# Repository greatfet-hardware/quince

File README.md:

# Quince
a 2.4 GHz SDR neighbor for GreatFET using 1-bit ADCs

Quince is a GreatFET neighbor that serves as a Software Defined Radio (SDR) receiver for the 2.4 GHz band using a 1-bit sampling technique.  It is intended specifically to enable all-channel Bluetooth monitoring, but it should support additional uses.

Quince features the TLV3502 dual comparator and an RF section based on the AD8347 quadrature demodulator.  Synthesis of a 2.4 GHz Local Oscillator (LO) is provided by ADF4360-0.  The 1-bit quadrature signals are sampled at 80+ Msps by the SGPIO peripheral on [Azalea](https://github.com/greatfet-hardware/azalea).

Channelization and demodulation are done in software on the host computer, but it may be necessary to add an FPGA to Quince in order to achieve real-time simultaneous monitoring of all Bluetooth channels.  The host software will likely be a rewrite of [gr-bluetooth](https://github.com/greatscottgadgets/gr-bluetooth) using [libbtbb](https://github.com/greatscottgadgets/libbtbb) (the core of software for [Ubertooth](https://greatscottgadgets.com/ubertoothone/)).

## Project Status

The first hardware prototype that achieves proof-of-concept has been assembled.  Software work is required before determining what changes are needed in the next hardware revision.

## Viewing or Modifying the Design

Required KiCad dependency:

https://github.com/greatscottgadgets/gsg-kicad-lib

If you are using git, the preferred way to install gsg-kicad-lib is to use the
submodule:

```
git submodule init && git submodule update
```

## Hardware Development Notes

Lower cost comparators that may have sufficient bandwidth:
* TLV3202, comparator, $0.60
* NCS2250, single, $0.20

It might be more cost-effective to use a wireless transmitter or transceiver IC to generate the LO, such as:
* CC2500
* ADF7242 (used on [Lucky Bamboo](https://github.com/greatfet-hardware/luckybamboo))

As an alternative to the comparators (and possibly to the quadrature demodulator as well) we may investigate the use of LVDS input on an FPGA.  This would be the preferred solution if an FPGA ends up on the board anyway for channelization.

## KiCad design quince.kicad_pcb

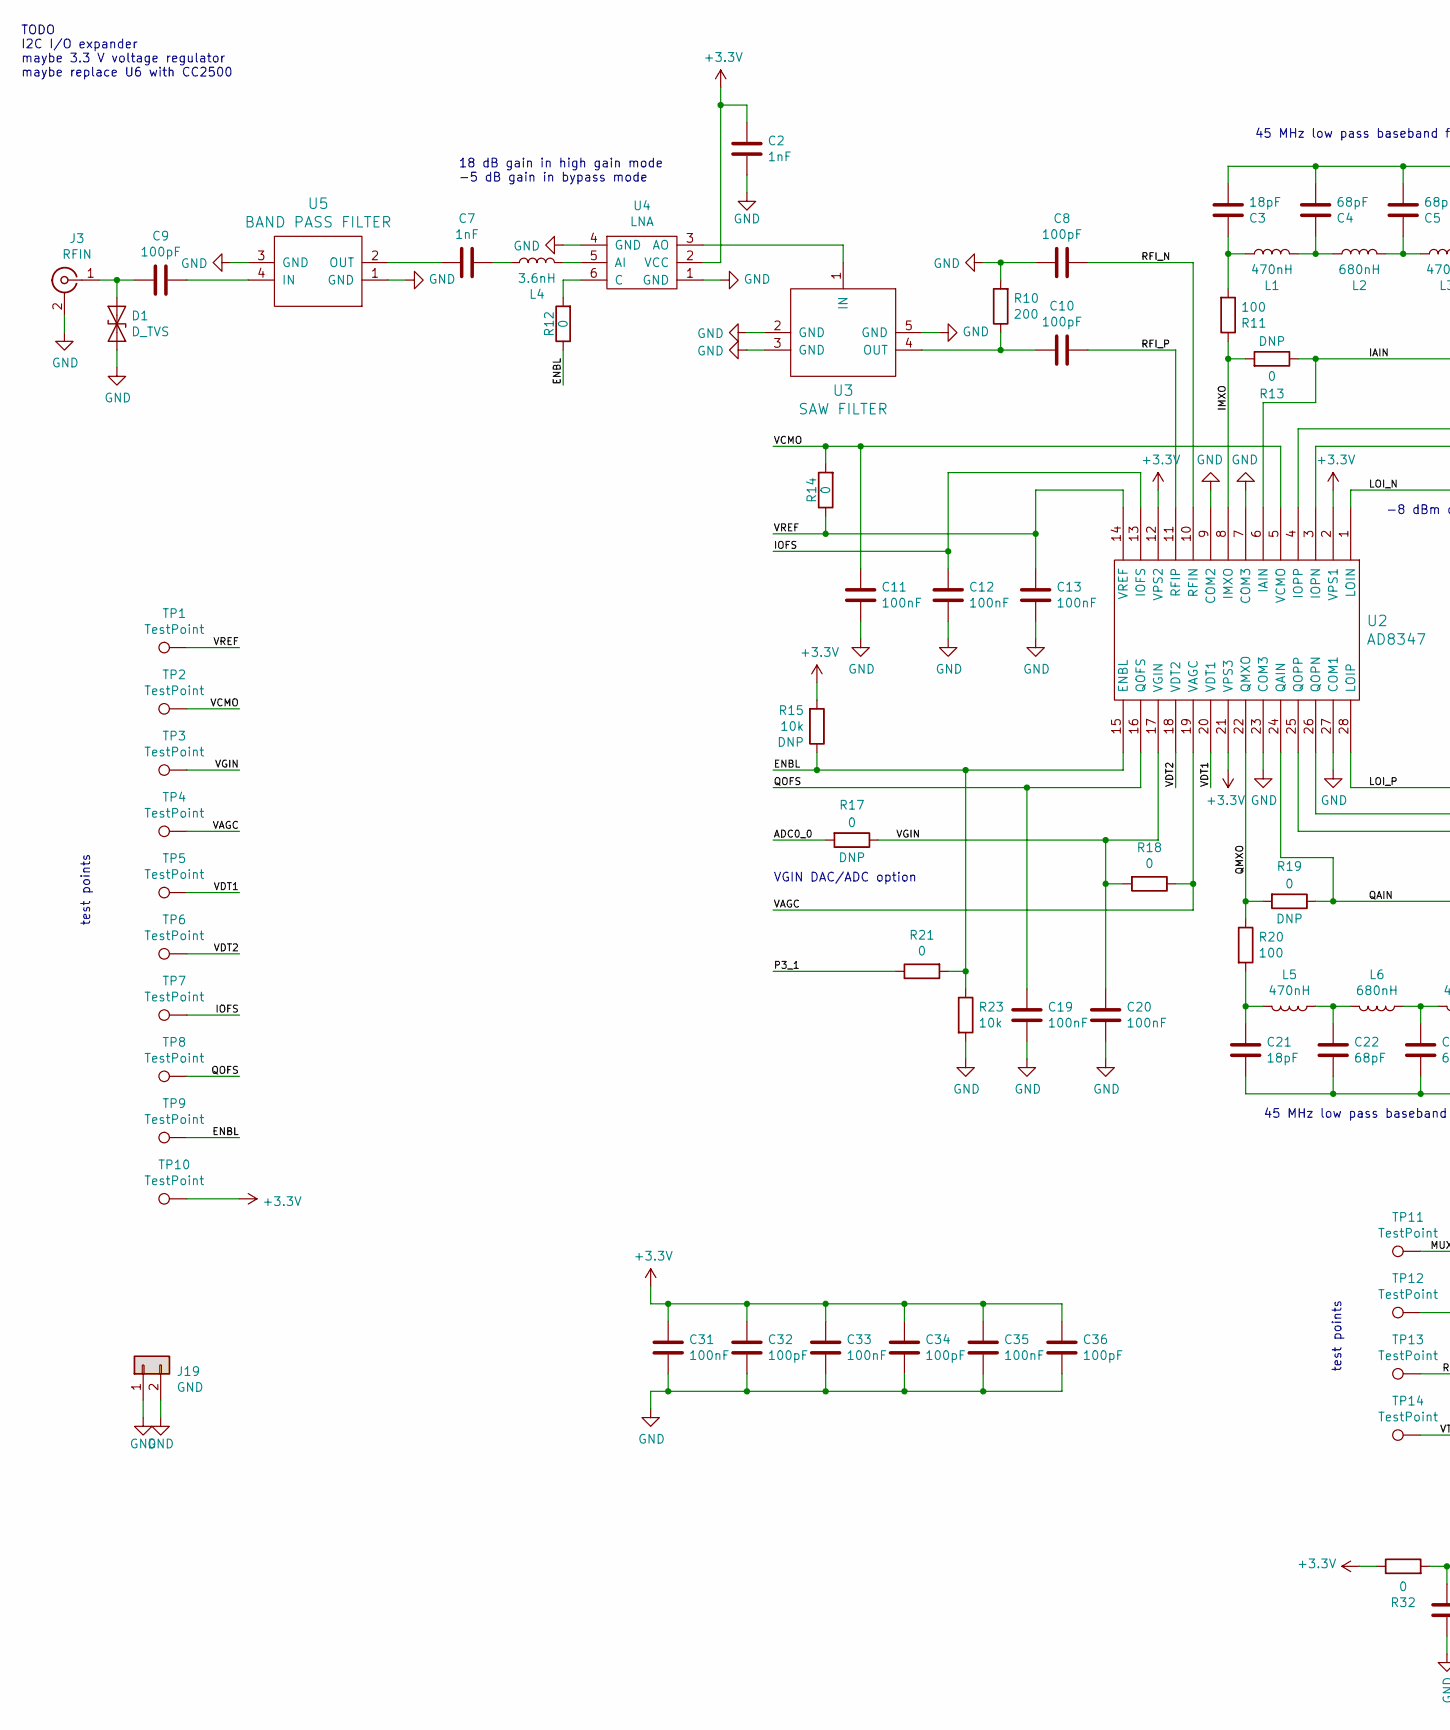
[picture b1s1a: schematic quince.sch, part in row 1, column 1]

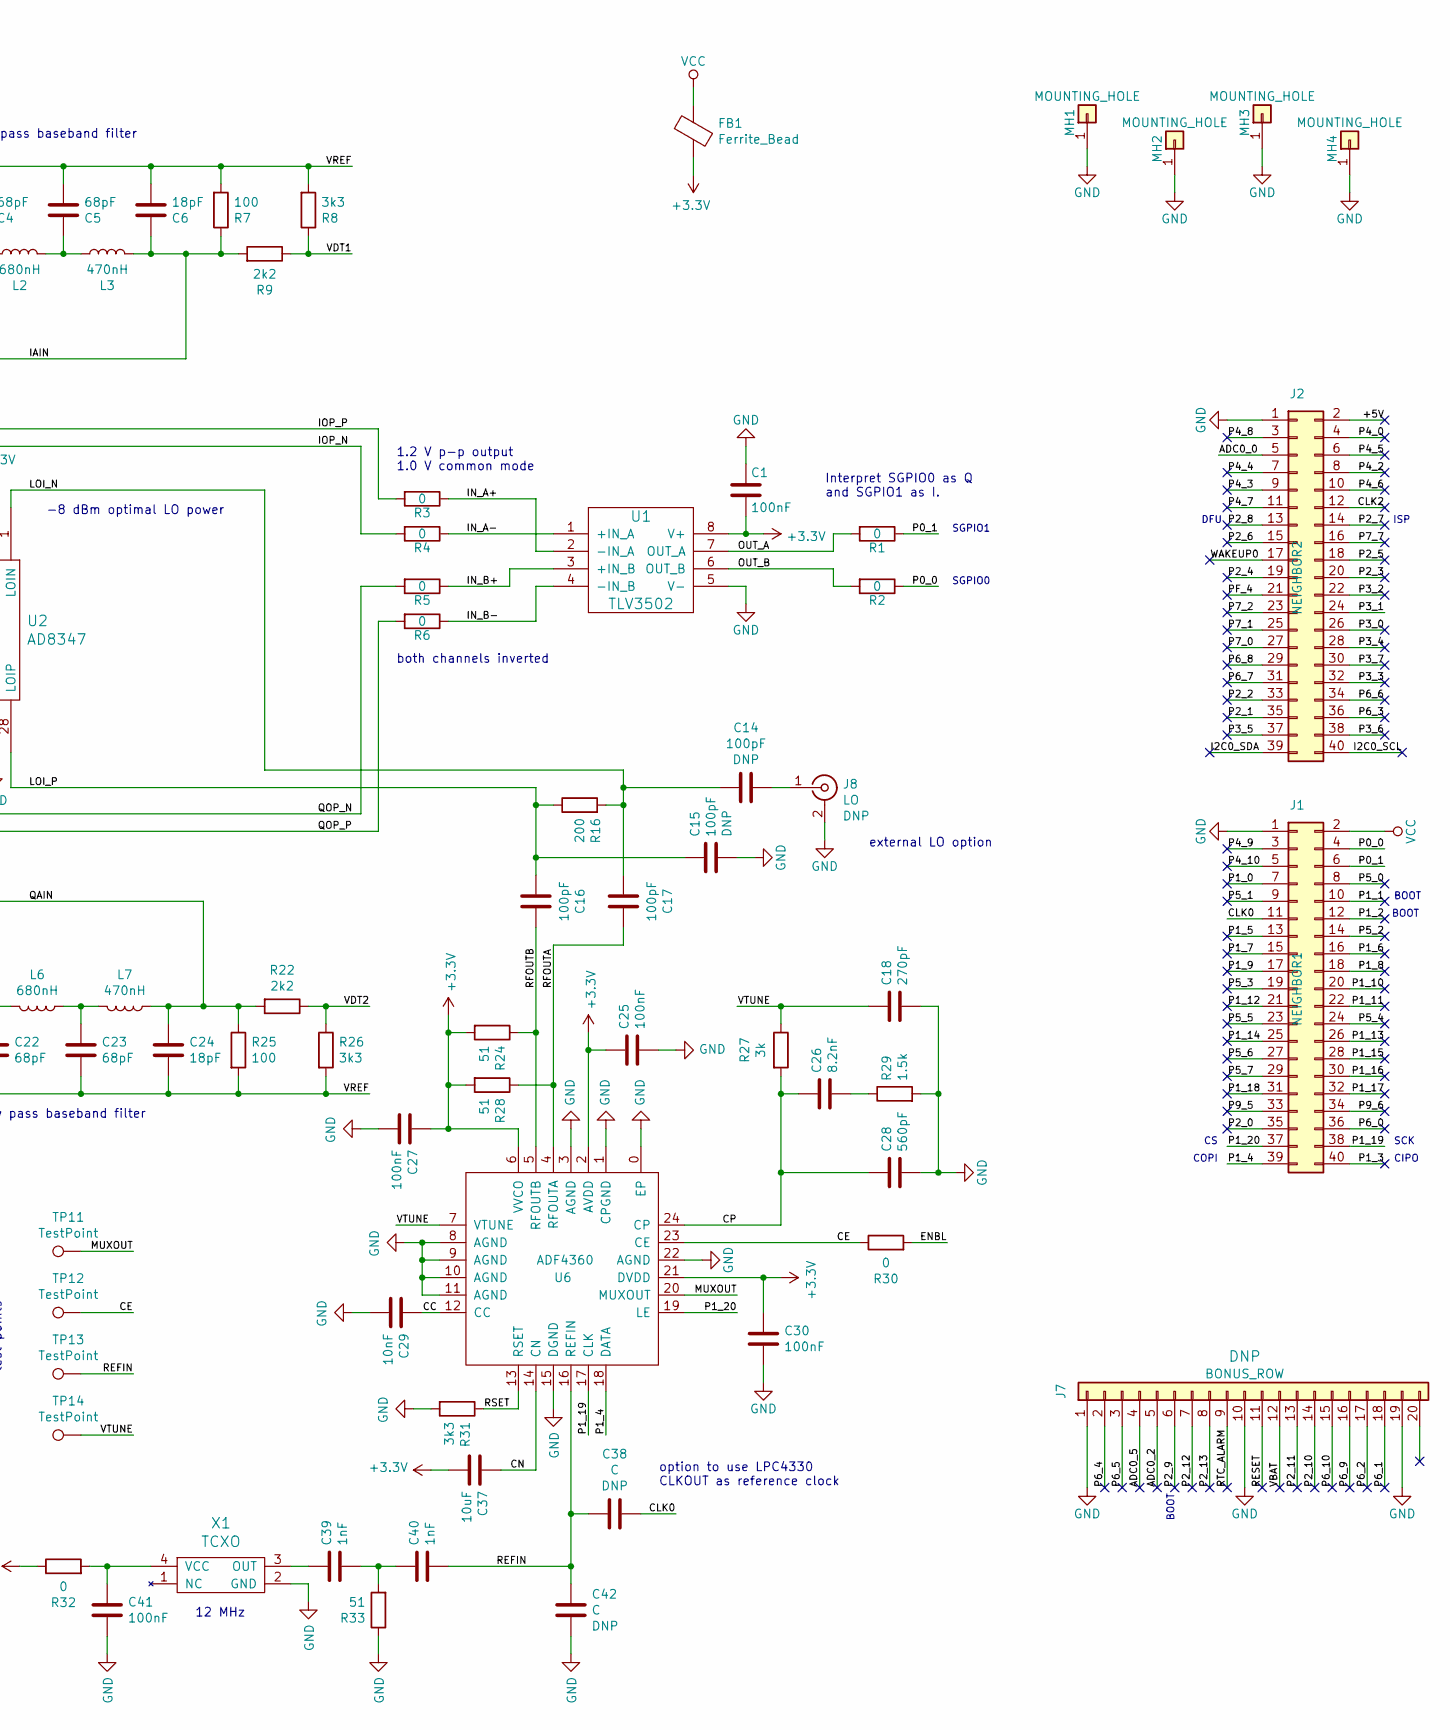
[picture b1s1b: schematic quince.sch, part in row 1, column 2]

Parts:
C1, C11, C12, C13, C19, C20, C25, C27, C30, C31, C33, C35, C41: 100nF; 0402; Part Number CL05A104MP5NNNC
C2, C7, C39, C40: 1nF; 0402; Part Number UMK105B7102KV-F
C3, C6, C21, C24: 18pF; 0402; Part Number CC0402JRNPO9BN180
C4, C5, C22, C23: 68pF; 0402; Part Number CL05C680JB5NNNC
C8, C9, C10, C14, C15, C16, C17, C32, C34, C36: 100pF; 0402; Part Number CL05C101JB5NNNC
C18: 270pF; 0402; Part Number CL05B271KB5NNNC
C26: 8.2nF; 0402; Part Number CC0402KRX7R7BB822
C28: 560pF; 0402; Part Number CL05B561KB5NNNC
C29: 10nF; 0402; Part Number CL05B103KB5NNNC
C37: 10uF; 0805; Part Number CL21A106KPFNNNG
C38, C42: C; 0402
D1: D_TVS; 0402; Part Number LXES15AAA1-153
FB1: Ferrite_Bead; 0805; Part Number BLM21PG221SN1D
J1: NEIGHBOR1; HEADER-2x20; Part Number SSQ-120-23-G-D
J2: NEIGHBOR2; HEADER-2x20; Part Number SSQ-120-23-G-D
J3: RFIN; SMA-EDGE; Part Number CONREVSMA003.062
J7: BONUS_ROW; HEADER-1x20; Part Number SSQ-120-23-G-S
J8: LO; SMA-VERTICAL; Part Number 5-1814832-1
J19: GND; HEADER-1x2
L1, L3, L5, L7: 470nH; 0402; Part Number LK1005R47K-TV
L2, L6: 680nH; 0402; Part Number LK1005R68K-TV
L4: 3.6nH; 0402; Part Number HK10053N6S-T
MH1, MH2, MH3, MH4: MOUNTING_HOLE; HOLE126MIL-COPPER
R1, R2, R3, R4, R5, R6, R12, R13, R14, R17, R18, R19, R21, R30, R32: 0; 0402; Part Number RC0402JR-070RL
R7, R11, R20, R25: 100; 0402; Part Number RC0402JR-07100RL
R8, R26, R31: 3k3; 0402; Part Number RC0402JR-073K3L
R9, R22: 2k2; 0402; Part Number RC0402JR-072K2L
R10, R16: 200; 0402; Part Number RC0402JR-07200RL
R15, R23: 10k; 0402; Part Number RC0402JR-0710KL
R24, R28, R33: 51; 0402; Part Number RC0402JR-0751RL
R27: 3k; 0402; Part Number RC0402JR-073KL
R29: 1.5k; 0402; Part Number RC0402JR-071K5L
TP1, TP2, TP3, TP4, TP5, TP6, TP7, TP8, TP9, TP10, TP11, TP12, TP13, TP14: TestPoint; TESTPOINT-50MIL
U1: TLV3502; SOIC8-154; Part Number TLV3502AIDR
U2: AD8347; TSSOP28; Part Number AD8347ARUZ-REEL7
U3: SAW FILTER; B9413; Part Number B39242B9413K610
U4: LNA; BGA7H1N6; Part Number BGA5H1BN6E6327XTSA1
U5: BAND PASS FILTER; 2450BP39D100C; Part Number 2450BP39D100CE
U6: ADF4360; QFN24-4; Part Number ADF4360-0BCPZ
X1: TCXO; XTAL5.0x3.2mm; Part Number FT5HNBPK12.0-T1

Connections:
+3V3: C1.2, C2.2, C25.1, C27.1, C30.1, C31.1, C32.2, C33.1, C34.2, C35.1, C36.2, C37.2, FB1.2, R15.2, R24.2, R28.2, R32.1, TP10.1, U1.8 (V+), U2.2 (VPS1), U2.12 (VPS2), U2.21 (VPS3), U4.2 (VCC), U6.2 (AVDD), U6.6 (VVCO), U6.21 (DVDD)
/+5V: J2.2
/ADC0_0: J2.5, R17.2
/ADC0_2: J7.5
/ADC0_5: J7.4
/CC: C29.1, U6.12 (CC)
/CE: R30.1, TP12.1, U6.23 (CE)
/CLK0: C38.2, J1.11
/CLK2: J2.12
/CN: C37.1, U6.14 (CN)
/CP: C26.2, C28.2, R27.2, U6.24 (CP)
/ENBL: R12.1, R15.1, R21.2, R23.1, R30.2, TP9.1, U2.15 (ENBL)
/I2C0_SCL: J2.40
/I2C0_SDA: J2.39
/IAIN: C6.1, L3.1, R7.1, R9.2, R13.1, U2.6 (IAIN)
/IMXO: R11.1, R13.2, U2.8 (IMXO)
/IN_A+: R3.1, U1.2 (-IN_A)
/IN_A-: R4.1, U1.1 (+IN_A)
/IN_B+: R5.1, U1.3 (+IN_B)
/IN_B-: R6.1, U1.4 (-IN_B)
/IOFS: C12.1, TP7.1, U2.13 (IOFS)
/IOP_N: R4.2, U2.3 (IOPN)
/IOP_P: R3.2, U2.4 (IOPP)
/LOI_N: C14.2, C17.2, R16.2, U2.1 (LOIN)
/LOI_P: C15.2, C16.2, R16.1, U2.28 (LOIP)
/MUXOUT: TP11.1, U6.20 (MUXOUT)
/OUT_A: R1.2, U1.7 (OUT_A)
/OUT_B: R2.2, U1.6 (OUT_B)
/P0_0: J1.4, R2.1
/P0_1: J1.6, R1.1
/P1_0: J1.7
/P1_1: J1.10
/P1_2: J1.12
/P1_3: J1.40
/P1_4: J1.39, U6.18 (DATA)
/P1_5: J1.13
/P1_6: J1.16
/P1_7: J1.15
/P1_8: J1.18
/P1_9: J1.17
/P1_10: J1.20
/P1_11: J1.22
/P1_12: J1.21
/P1_13: J1.26
/P1_14: J1.25
/P1_15: J1.28
/P1_16: J1.30
/P1_17: J1.32
/P1_18: J1.31
/P1_19: J1.38, U6.17 (CLK)
/P1_20: J1.37, U6.19 (LE)
/P2_0: J1.35
/P2_1: J2.35
/P2_2: J2.33
/P2_3: J2.20
/P2_4: J2.19
/P2_5: J2.18
/P2_6: J2.15
/P2_7: J2.14
/P2_8: J2.13
/P2_9: J7.6
/P2_10: J7.14
/P2_11: J7.13
/P2_12: J7.7
/P2_13: J7.8
/P3_0: J2.26
/P3_1: J2.24, R21.1
/P3_2: J2.22
/P3_3: J2.32
/P3_4: J2.28
/P3_5: J2.37
/P3_6: J2.38
/P3_7: J2.30
/P4_0: J2.4
/P4_2: J2.8
/P4_3: J2.9
/P4_4: J2.7
/P4_5: J2.6
/P4_6: J2.10
/P4_7: J2.11
/P4_8: J2.3
/P4_9: J1.3
/P4_10: J1.5
/P5_0: J1.8
/P5_1: J1.9
/P5_2: J1.14
/P5_3: J1.19
/P5_4: J1.24
/P5_5: J1.23
/P5_6: J1.27
/P5_7: J1.29
/P6_0: J1.36
/P6_1: J7.18
/P6_2: J7.17
/P6_3: J2.36
/P6_4: J7.2
/P6_5: J7.3
/P6_6: J2.34
/P6_7: J2.31
/P6_8: J2.29
/P6_9: J7.16
/P6_10: J7.15
/P7_0: J2.27
/P7_1: J2.25
/P7_2: J2.23
/P7_7: J2.16
/P9_5: J1.33
/P9_6: J1.34
/PF_4: J2.21
/QAIN: C24.1, L7.1, R19.1, R22.2, R25.1, U2.24 (QAIN)
/QMXO: R19.2, R20.1, U2.22 (QMXO)
/QOFS: C19.1, TP8.1, U2.16 (QOFS)
/QOP_N: R5.2, U2.26 (QOPN)
/QOP_P: R6.2, U2.25 (QOPP)
/REFIN: C38.1, C40.2, C42.2, TP13.1, U6.16 (REFIN)
/RESET: J7.11
/RFI_N: C8.1, U2.10 (RFIN)
/RFI_P: C10.1, U2.11 (RFIP)
/RFOUTA: C17.1, R28.1, U6.4 (RFOUTA)
/RFOUTB: C16.1, R24.1, U6.5 (RFOUTB)
/RSET: R31.1, U6.13 (RSET)
/RTC_ALARM: J7.9
/VAGC: R18.1, TP4.1, U2.19 (VAGC)
/VBAT: J7.12
/VCMO: C11.1, R14.2, TP2.1, U2.5 (VCMO)
/VDT1: R8.1, R9.1, TP5.1, U2.20 (VDT1)
/VDT2: R22.1, R26.1, TP6.1, U2.18 (VDT2)
/VGIN: C20.1, R17.1, R18.2, TP3.1, U2.17 (VGIN)
/VREF: C3.2, C4.2, C5.2, C6.2, C13.1, C21.2, C22.2, C23.2, C24.2, R7.2, R8.2, R14.1, R25.2, R26.2, TP1.1, U2.14 (VREF)
/VTUNE: C18.2, R27.1, TP14.1, U6.7 (VTUNE)
/WAKEUP0: J2.17
GND: C1.1, C2.1, C8.2, C11.2, C12.2, C13.2, C15.1, C18.1, C19.2, C20.2, C25.2, C27.2, C28.1, C29.2, C30.2, C31.2, C32.1, C33.2, C34.1, C35.2, C36.1, C41.2, C42.1, D1.2 (A2), J1.1, J2.1, J3.2 (Ext), J7.1, J7.10, J7.19, J8.2 (Ext), J19.1, J19.2, MH1.1, MH2.1, MH3.1, MH4.1, R10.2, R23.2, R29.2, R31.2, R33.1, U1.5 (V-), U2.7 (COM3), U2.9 (COM2), U2.23 (COM3), U2.27 (COM1), U3.2 (GND), U3.3 (GND), U3.5 (GND), U4.1 (GND), U4.4 (GND), U5.1 (GND), U5.3 (GND), U6.0 (EP), U6.1 (CPGND), U6.3 (AGND), U6.8 (AGND), U6.9 (AGND), U6.10 (AGND), U6.11 (AGND), U6.15 (DGND), U6.22 (AGND), X1.2 (GND)
unnamed: C3.1, L1.2, R11.2
unnamed: C4.1, L1.1, L2.2
unnamed: C5.1, L2.1, L3.2
unnamed: C7.1, U5.2 (OUT)
unnamed: C7.2, L4.2
unnamed: C9.1, U5.4 (IN)
unnamed: C9.2, D1.1 (A1), J3.1 (In)
unnamed: C10.2, R10.1, U3.4 (OUT)
unnamed: C14.1, J8.1 (In)
unnamed: C21.1, L5.2, R20.2
unnamed: C22.1, L5.1, L6.2
unnamed: C23.1, L6.1, L7.2
unnamed: C26.1, R29.1
unnamed: C39.1, X1.3 (OUT)
unnamed: C39.2, C40.1, R33.2
unnamed: C41.1, R32.2, X1.4 (VCC)
unnamed: L4.1, U4.5 (AI)
unnamed: R12.2, U4.6 (C)
unnamed: U3.1 (IN), U4.3 (AO)
VCC: FB1.1, J1.2

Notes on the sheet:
CIPO
COPI
SCK
ISP
DFU
BOOT
SGPIO0
SGPIO1
45 MHz low pass baseband filter
both channels inverted
1.2 V p-p output 1.0 V common mode
external LO option
-8 dBm optimal LO power
test points
VGIN DAC/ADC option
Interpret SGPIO0 as Q and SGPIO1 as I.
18 dB gain in high gain mode -5 dB gain in bypass mode
TODO I2C I/O expander maybe 3.3 V voltage regulator maybe replace U6 with CC2500
option to use LPC4330 CLKOUT as reference clock
12 MHz

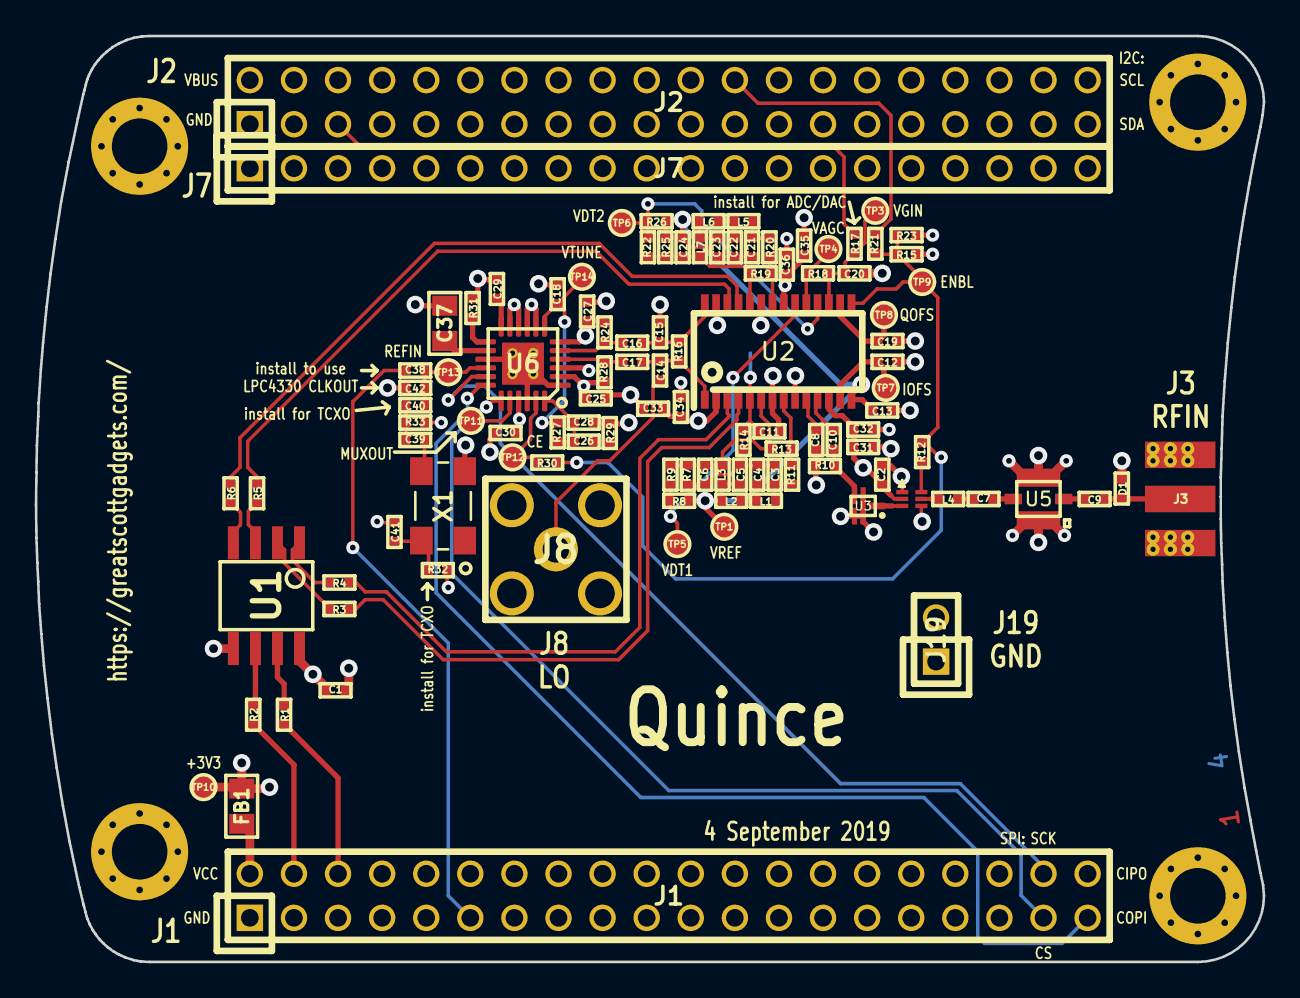
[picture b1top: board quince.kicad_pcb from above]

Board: 4 copper layers, 70.7 x 53.3 mm, 115 parts (1 on the bottom side), 67 nets.

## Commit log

2019-05-27 split quince into separate repository
2019-05-27 updated README.md to be quince-specific
2019-08-31 updated to KiCad 5.1
2019-09-01 add RF section to schematic copied from Daisho/rx2400ism
2019-09-01 add sym-lib-table, update .gitignore for KiCad 5.1
2019-09-01 add frequency synthesizer
2019-09-02 change U4 LNA from MAX2641 to BGA5H1BN6 to reduce cost and part count
2019-09-03 assign footprints
2019-09-04 complete layout
2019-09-04 use proper test point symbols
2019-09-04 assign less confusing names to inner copper layers
2019-09-06 move information from greatfet wiki to README
2019-09-23 select parts
2019-10-02 fix U1 part selection
2019-10-25 README: correct URLs for other neighbors
2019-10-25 README update
2020-07-03 adopt OSHWA convention for SPI signal names https://www.oshwa.org/a-resolution-to-redefine-spi-signal-names

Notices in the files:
quince.sch:
Copyright 2019 Great Scott Gadgets
License: BSD-3-Clause
